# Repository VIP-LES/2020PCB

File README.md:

# 2020PCB
A repository for PCB designs for 2020.

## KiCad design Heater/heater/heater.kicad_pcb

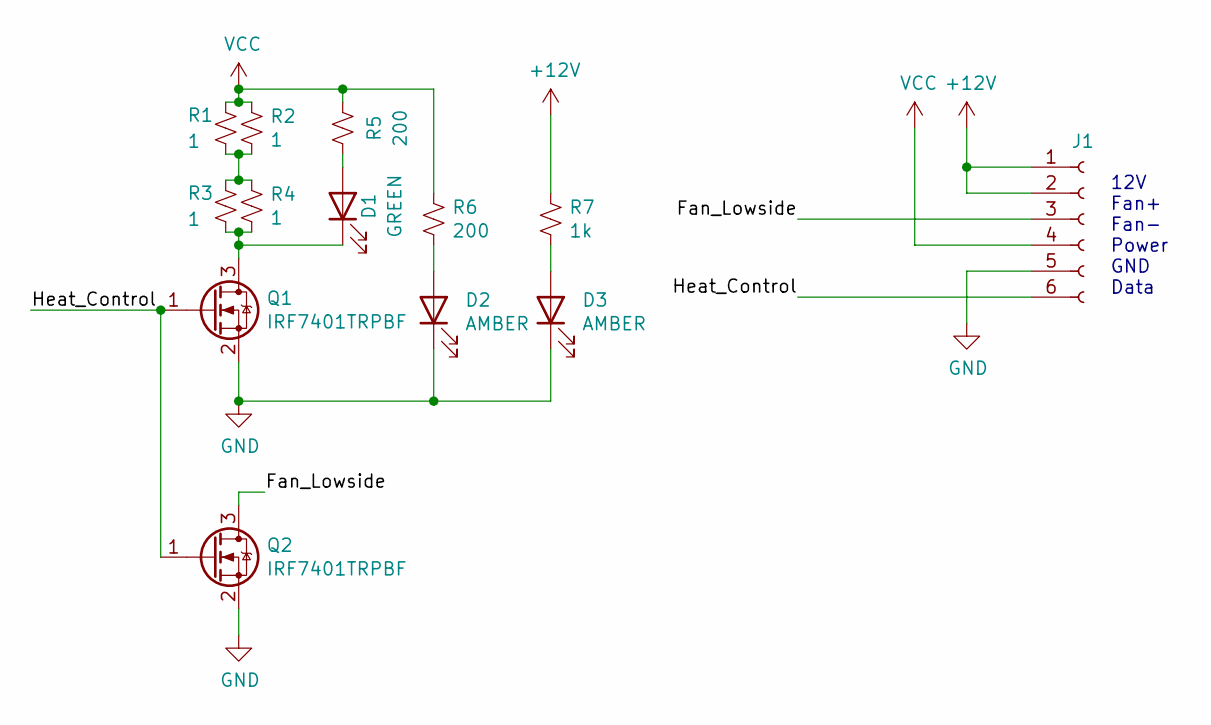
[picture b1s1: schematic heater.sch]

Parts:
D1: GREEN; LED_0805_2012Metric_Pad1.15x1.40mm_HandSolder
D2, D3: AMBER; LED_0805_2012Metric_Pad1.15x1.40mm_HandSolder
J1: TerminalBlock_Phoenix_MKDS-1,5-6_1x06_P5.00mm_Horizontal
Q1, Q2: IRF7401TRPBF; SO-8_3.9x4.9mm_P1.27mm
R1, R2, R3, R4: 1; R_Axial_Power_L25.0mm_W9.0mm_P30.48mm
R5, R6: 200; R_0805_2012Metric_Pad1.15x1.40mm_HandSolder
R7: 1k; R_0805_2012Metric_Pad1.15x1.40mm_HandSolder

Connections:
+12V: J1.1, J1.2, R7.1
/Fan_Lowside: J1.3, Q2.3 (D)
/Heat_Control: J1.6, Q1.1 (G), Q2.1 (G)
GND: D2.1 (K), D3.1 (K), J1.5, Q1.2 (S), Q2.2 (S)
unnamed: D1.1 (K), Q1.3 (D), R3.2, R4.2
unnamed: D1.2 (A), R5.1
unnamed: D2.2 (A), R6.2
unnamed: D3.2 (A), R7.2
unnamed: R1.2, R2.2, R3.1, R4.1
VCC: J1.4, R1.1, R2.1, R5.2, R6.1

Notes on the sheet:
12V Fan+ Fan- Power GND Data

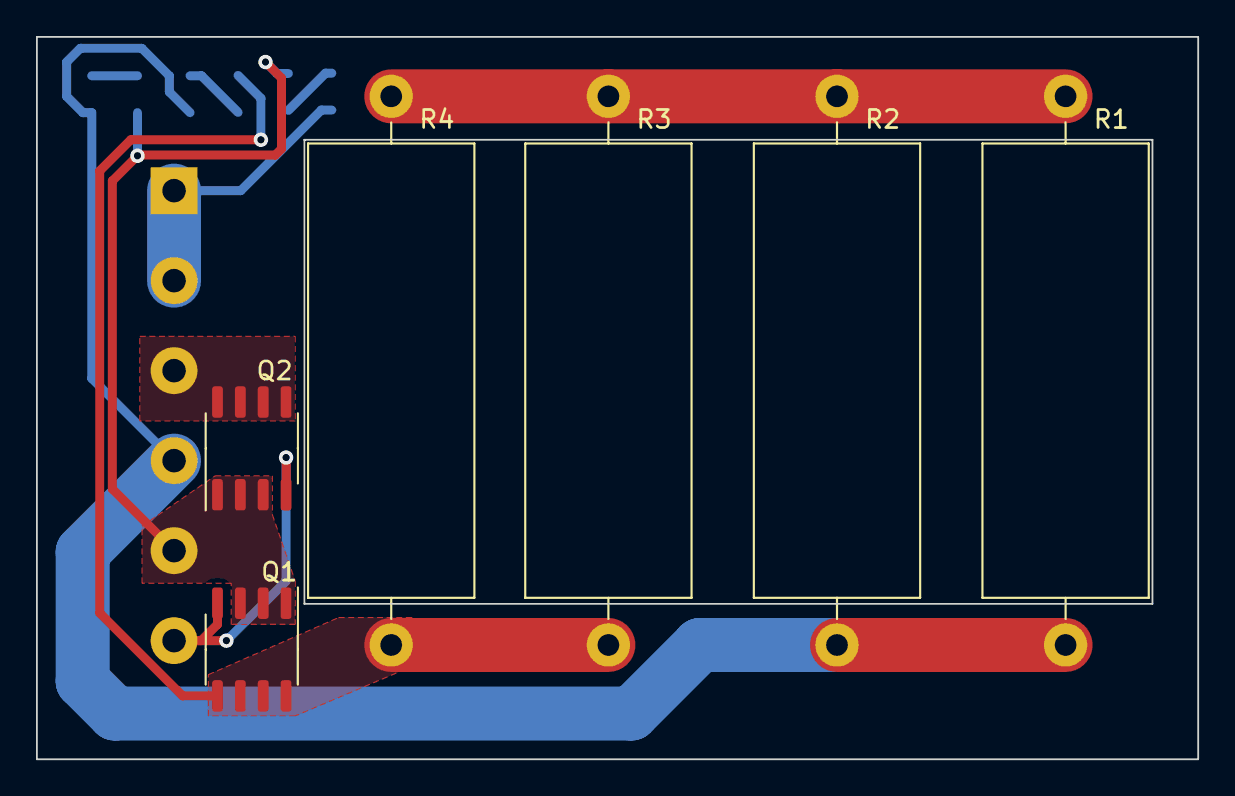
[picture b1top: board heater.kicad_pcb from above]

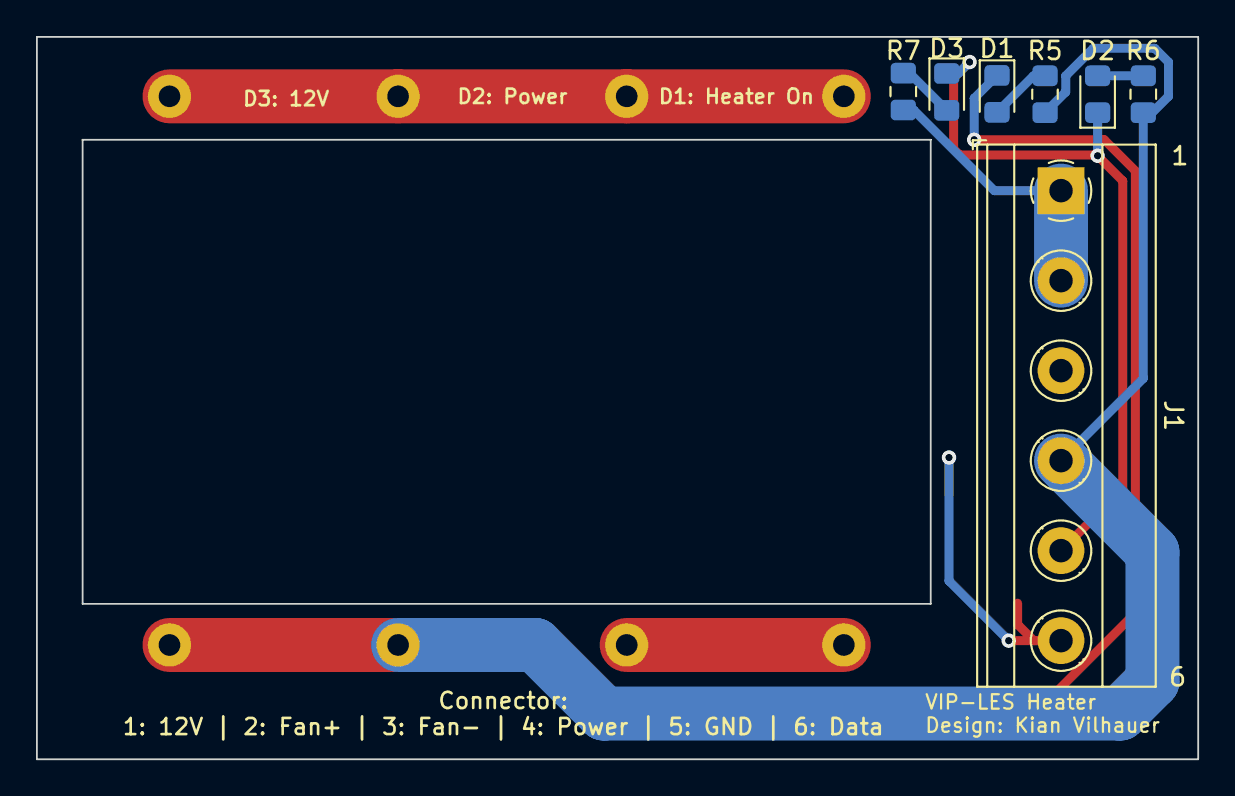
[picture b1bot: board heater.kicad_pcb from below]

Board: 2 copper layers, 64.5 x 40.1 mm, 13 parts (7 on the bottom side), 10 nets.

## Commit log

2020-10-12 Update heater pcb
2020-10-16 update heater pcb
    Heater pcb now includes 12V for fan, and a FET to switch the fans on and off
